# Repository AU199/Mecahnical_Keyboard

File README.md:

# Mecahnical Keyboard
I made this projects because I wanted to learn how software and hardware come together inside something as simple keyboard (Which I found wasn't simple at all). I wanted to also learn how to make a PCB and how to CAD with better practices. This is a Mechanical keyboard that utilizes both a main chip and a "slave" chip (a chip made to work as if it were just an i/o extender). This uses a diode-matrix for the sensing and uses the SDA and SCL channels on the "slave" chip to read and understand. 

BOM (Used an program for this to convert to a table in a .md file)
| Item                            | Description                                                 | Quantity | Total Price | shipping                                                                                                                                          | Link                                                                                                                                                                                                                                                                                                                                                                                                                                                                                                                                                                                                                                                                                                                                                                                                                                                                         | Running Total | Comments                                          |
| ------------------------------- | ----------------------------------------------------------- | -------- | ----------- | ------------------------------------------------------------------------------------------------------------------------------------------------- | ---------------------------------------------------------------------------------------------------------------------------------------------------------------------------------------------------------------------------------------------------------------------------------------------------------------------------------------------------------------------------------------------------------------------------------------------------------------------------------------------------------------------------------------------------------------------------------------------------------------------------------------------------------------------------------------------------------------------------------------------------------------------------------------------------------------------------------------------------------------------------- | ------------- | ------------------------------------------------- |
| Kailh Hotswap Switches (70 PCS) | Need for the mechanical Keyboard switches                   | 1        | $4.71       |                                                                                                                                                   | https://www.aliexpress.us/item/3256807290300019.html?spm=a2g0o.cart.0.0.655c38dakew0gR&mp=1&pdp_npi=5%40dis%21USD%21USD%2010.00%21USD%205.00%21%21USD%205.00%21%21%21%402103212b17669562373644915e8654%2112000040910888023%21ct%21US%216957464215%21%211%210&_gl=1*7n8lx*_gcl_aw*R0NMLjE3NjY5NTY1MjkuQ2owS0NRaUF4OFBLQmhEMUFSSXNBS3NtR2JmVFB0Uld6WHhSZGZYQmY2YmJCM0ppSWhiVndEci14TE1SelRfRDM4Y1R5UERmcTU4enRMc2FBaENJRUFMd193Y0I.*_gcl_dc*R0NMLjE3NjY5NTY1MjkuQ2owS0NRaUF4OFBLQmhEMUFSSXNBS3NtR2JmVFB0Uld6WHhSZGZYQmY2YmJCM0ppSWhiVndEci14TE1SelRfRDM4Y1R5UERmcTU4enRMc2FBaENJRUFMd193Y0I.*_gcl_au*MTg0MTgyOTEyNy4xNzY1OTI2NjE1*_ga*MTA1MDk4OTI5NS4xNzY2OTU0OTQ3*_ga_VED1YSGNC7*czE3NjY5NTQ5NDckbzEkZzEkdDE3NjY5NTY3ODgkajYwJGwwJGgw&gatewayAdapt=glo2usa                                                                                                                    | $4.71         |                                                   |
| 0.91 INCH OLED DISPLAY MODULE   | Display Module added for display functionallity             | 1        | $2.40       |                                                                                                                                                   | https://www.aliexpress.us/item/3256807115924372.html?spm=a2g0o.cart.0.0.200938daSMtqfN&mp=1&pdp_npi=6%40dis%21USD%21USD%204.81%21USD%202.36%21%21USD%202.08%21%21%21%402101d97817676331257023363ef25d%2112000040130675889%21ct%21US%216957464215%21%211%210%21&_gl=1*uoe70x*_gcl_aw*R0NMLjE3NjcwMjY4OTMuQ2owS0NRaUF4OFBLQmhEMUFSSXNBS3NtR2JmQUFHcUtNY3B5MU8xZEpYcC1KQmpCRi1yMkM3VEswRUFtMGNUUmZReU1lM1lSSjliV3RzY2FBakQ5RUFMd193Y0I.*_gcl_dc*R0NMLjE3NjcwMjY4OTMuQ2owS0NRaUF4OFBLQmhEMUFSSXNBS3NtR2JmQUFHcUtNY3B5MU8xZEpYcC1KQmpCRi1yMkM3VEswRUFtMGNUUmZReU1lM1lSSjliV3RzY2FBakQ5RUFMd193Y0I.*_gcl_au*MTg0MTgyOTEyNy4xNzY1OTI2NjE1*_ga*MTE3MjgzNDE0NC4xNzY3NTcxNTAx*_ga_VED1YSGNC7*czE3Njc2MzMxMTgkbzQkZzEkdDE3Njc2MzMxMjYkajUyJGwwJGgw&gatewayAdapt=glo2usa#nav-description                                                                                                 | $7.07         |                                                   |
| MCP23017-E/SO                   | I/O expander that I need in order to make the full keyboard | 1        | $4.99       |                                                                                                                                                   | https://www.aliexpress.us/item/3256810374801839.html?spm=a2g0o.productlist.main.2.77f5IXMhIXMhAF&algo_pvid=e8501886-1288-485f-a514-a1c879ddfb29&algo_exp_id=e8501886-1288-485f-a514-a1c879ddfb29-1&pdp_ext_f=%7B%22order%22%3A%22-1%22%2C%22eval%22%3A%221%22%2C%22fromPage%22%3A%22search%22%7D&pdp_npi=6%40dis%21USD%2113.11%210.99%21%21%2191.32%216.91%21%402101f11417669549847548423eec63%2112000052856422464%21sea%21US%210%21ABX%211%210%21n_tag%3A-29910%3Bd%3A1e4e634d%3Bm03_new_user%3A-29895%3BpisId%3A5000000187461913&curPageLogUid=8ompgAlH495t&utparam-url=scene%3Asearch%7Cquery_from%3A%7Cx_object_id%3A1005010561116591%7C_p_origin_prod%3A                                                                                                                                                                                                                | $12.06        |                                                   |
| XIAO-nRF52840                   | Main Chip of this keyboard                                  | 1        | $11.77      |                                                                                                                                                   | https://www.aliexpress.us/item/3256808117851584.html?spm=a2g0o.productlist.main.7.3ee7aNioaNioHj&algo_pvid=a97ae570-3fd6-4518-abb6-32d770b1e93e&algo_exp_id=a97ae570-3fd6-4518-abb6-32d770b1e93e-6&pdp_ext_f=%7B%22order%22%3A%22111%22%2C%22eval%22%3A%221%22%2C%22fromPage%22%3A%22search%22%7D&pdp_npi=6%40dis%21USD%2110.10%2110.10%21%21%2170.31%2170.31%21%402101df0e17669551094443275eda12%2112000044555521520%21sea%21US%210%21ABX%211%210%21n_tag%3A-29910%3Bd%3A1e4e634d%3Bm03_new_user%3A-29895&curPageLogUid=50eSLpqHWYKf&utparam-url=scene%3Asearch%7Cquery_from%3A%7Cx_object_id%3A1005008304166336%7C_p_origin_prod%3A                                                                                                                                                                                                                                        | $23.83        |                                                   |
| PCB & PCBA                      | The total price for both making the PCB and the PCBA        | 1        | $42.01      | $91.28 (FedEx Express (DDP), I can't do anything about the price, there is also a 10 dollar discount as such the grand total comes to be $123.85) | JLCPCB (CAN'T PROVIDE A LINK)                                                                                                                                                                                                                                                                                                                                                                                                                                                                                                                                                                                                                                                                                                                                                                                                                                                | $147.68       | includes Sales tax, shipping and customes duties  |
| Key Switch                      | Needed for typing                                           | 1        | $3.23       |                                                                                                                                                   | https://www.aliexpress.us/item/3256806499127042.html?spm=a2g0o.cart.0.0.119e38daoqse3D&mp=1&pdp_npi=5%40dis%21USD%21USD%2011.21%21USD%2011.21%21%21USD%2011.21%21%21%21%402101e80f17669585322435838ec12b%2112000038218653076%21ct%21US%216957464215%21%211%210&_gl=1*gffty9*_gcl_aw*R0NMLjE3NjY5NTgyNDguQ2owS0NRaUF4OFBLQmhEMUFSSXNBS3NtR2JmQUFHcUtNY3B5MU8xZEpYcC1KQmpCRi1yMkM3VEswRUFtMGNUUmZReU1lM1lSSjliV3RzY2FBakQ5RUFMd193Y0I.*_gcl_dc*R0NMLjE3NjY5NTgyNDguQ2owS0NRaUF4OFBLQmhEMUFSSXNBS3NtR2JmQUFHcUtNY3B5MU8xZEpYcC1KQmpCRi1yMkM3VEswRUFtMGNUUmZReU1lM1lSSjliV3RzY2FBakQ5RUFMd193Y0I.*_gcl_au*MTg0MTgyOTEyNy4xNzY1OTI2NjE1*_ga*MTA1MDk4OTI5NS4xNzY2OTU0OTQ3*_ga_VED1YSGNC7*czE3NjY5NTQ5NDckbzEkZzEkdDE3NjY5NTg1MzIkajUwJGwwJGgw&gatewayAdapt=glo2usa                                                                                                                 | $150.91       |                                                   |
| Key Caps                        | Needed to put on the swtiches                               | 1        | $8.77       |                                                                                                                                                   | https://www.aliexpress.us/item/3256804183268436.html?src=google&pdp_npi=4%40dis%21USD%2110.83%2110.83%21%21%21%21%21%40%2112000028934642287%21ppc%21%21%21&src=google&albch=shopping&acnt=179-224-6891&isdl=y&slnk=&plac=&mtctp=&albbt=Google_7_shopping&aff_platform=google&aff_short_key=_oFgTQeV&gclsrc=aw.ds&albagn=888888&ds_e_adid=&ds_e_matchtype=&ds_e_device=c&ds_e_network=x&ds_e_product_group_id=&ds_e_product_id=en3256804183268436&ds_e_product_merchant_id=563759696&ds_e_product_country=US&ds_e_product_language=en&ds_e_product_channel=online&ds_e_product_store_id=&ds_url_v=2&albcp=23114515373&albag=&isSmbAutoCall=false&needSmbHouyi=false&gad_source=1&gad_campaignid=23118775333&gbraid=0AAAABBR8xIeRvhWb_9Ku5wF_pep51_OBj&gclid=Cj0KCQiAx8PKBhD1ARIsAKsmGbfAAGqKMcpy1O1dJXp-JBjBF-r2C7TK0EAm0cTRfQyMe3YRJ9bWtscaAjD9EALw_wcB&gatewayAdapt=glo2usa | $159.68       |                                                   |
| Resistor Network (6PCS)         | Pull up Resistor chain                                      | 1        | $1.79       |                                                                                                                                                   | https://www.aliexpress.us/item/3256806684196291.html?spm=a2g0o.cart.0.0.655c38dakew0gR&mp=1&pdp_npi=5%40dis%21USD%21USD%202.70%21USD%201.78%21%21USD%201.78%21%21%21%402103212b17669562373644915e8654%2112000038573406947%21ct%21US%216957464215%21%211%210&_gl=1*1fbksrg*_gcl_aw*R0NMLjE3NjY5NTQ5NjAuQ2owS0NRaUF4OFBLQmhEMUFSSXNBS3NtR2JkbV9Wd1pDZUd1b0tJd0wyMzRhZ3BfWjdUb1V5MlZTeFBDbHkyYVUyby1vVXphWG84Uk1oc2FBdnY3RUFMd193Y0I.*_gcl_au*MTg0MTgyOTEyNy4xNzY1OTI2NjE1*_ga*MjI2OTg1MDkxLjE3NjY5NTU3NDY.*_ga_VED1YSGNC7*czE3NjY5NTU3NDUkbzEkZzEkdDE3NjY5NTY0NTUkajYwJGwwJGgw&gatewayAdapt=glo2usa                                                                                                                                                                                                                                                                            | $161.47       |                                                   |
| Soldering Wire (Lead Free)      | Needed For Soldering                                        | 1        | $3.65       |                                                                                                                                                   | https://www.aliexpress.us/item/3256810239367550.html?spm=a2g0o.productlist.main.3.6fae31a3JUGwVE&algo_pvid=2b9bc4d0-e253-4360-b2cb-9148e3e8c081&algo_exp_id=2b9bc4d0-e253-4360-b2cb-9148e3e8c081-2&pdp_ext_f=%7B%22order%22%3A%227%22%2C%22eval%22%3A%221%22%2C%22fromPage%22%3A%22search%22%7D&pdp_npi=6%40dis%21USD%217.54%210.99%21%21%2152.50%216.88%21%402101c44517669559046362254ed6dc%2112000052371160761%21sea%21US%216957464215%21ABX%211%210%21n_tag%3A-29910%3Bd%3A1e4e634d%3Bm03_new_user%3A-29895%3BpisId%3A5000000187461913&curPageLogUid=hSphYWSM5PaN&utparam-url=scene%3Asearch%7Cquery_from%3A%7Cx_object_id%3A1005010425682302%7C_p_origin_prod%3A                                                                                                                                                                                                         | $165.12       |                                                   |
| Stabalizers                     | Needed for the larger keys                                  | 1        | $6.77       | $16.50                                                                                                                                            | https://www.aliexpress.us/item/2251832533420646.html?spm=a2g0o.productlist.main.3.2c756ad92TU7VN&algo_pvid=b65fade0-7f1d-4251-948a-926cfa9af3fb&algo_exp_id=b65fade0-7f1d-4251-948a-926cfa9af3fb-2&pdp_ext_f=%7B%22order%22%3A%2217%22%2C%22eval%22%3A%221%22%2C%22fromPage%22%3A%22search%22%7D&pdp_npi=6%40dis%21USD%216.77%210.99%21%21%216.77%210.99%21%402101e2b617669566038303233e2e16%2165420166339%21sea%21US%216957464215%21ABX%211%210%21n_tag%3A-29910%3Bd%3A1e4e634d%3Bm03_new_user%3A-29895%3BpisId%3A5000000187461913&curPageLogUid=hNoizrgNcue8&utparam-url=scene%3Asearch%7Cquery_from%3A%7Cx_object_id%3A32719735398%7C_p_origin_prod%3A                                                                                                                                                                                                                    | $188.39       | includes Sales tax and shipping                   |
|                                 |
# SHIPPING PRICE PROOF (Price is a little different since I had to make a new order, but the delivery method is still the same)   

# PCB Image

#CAD Image

# 3D Render '0'

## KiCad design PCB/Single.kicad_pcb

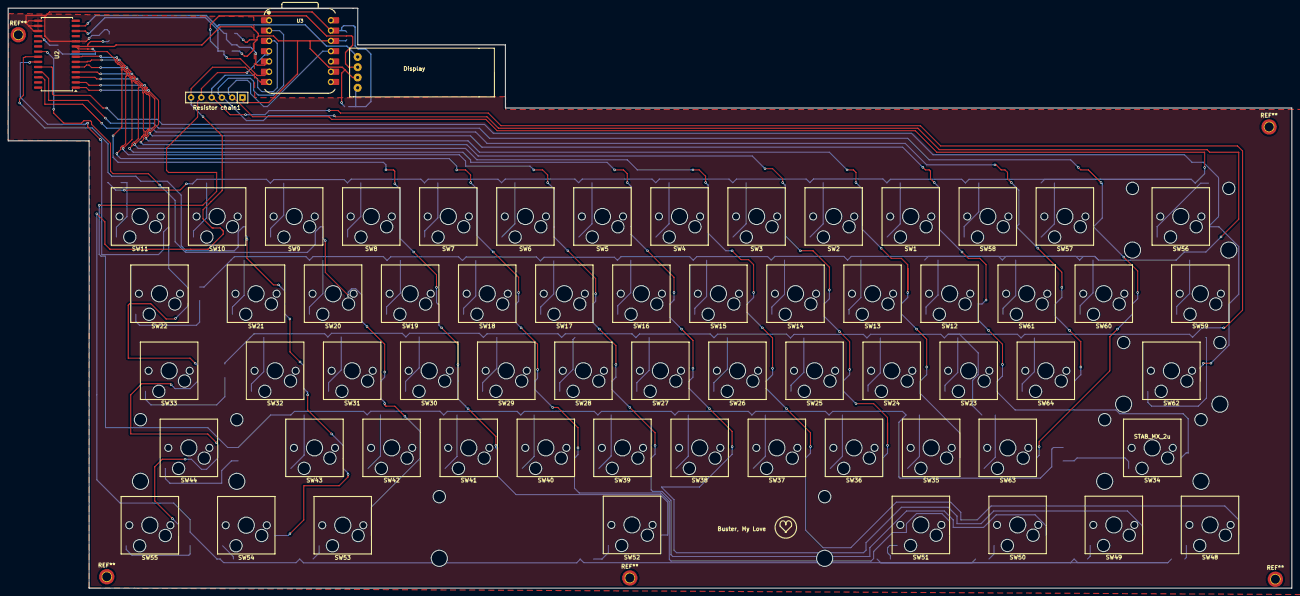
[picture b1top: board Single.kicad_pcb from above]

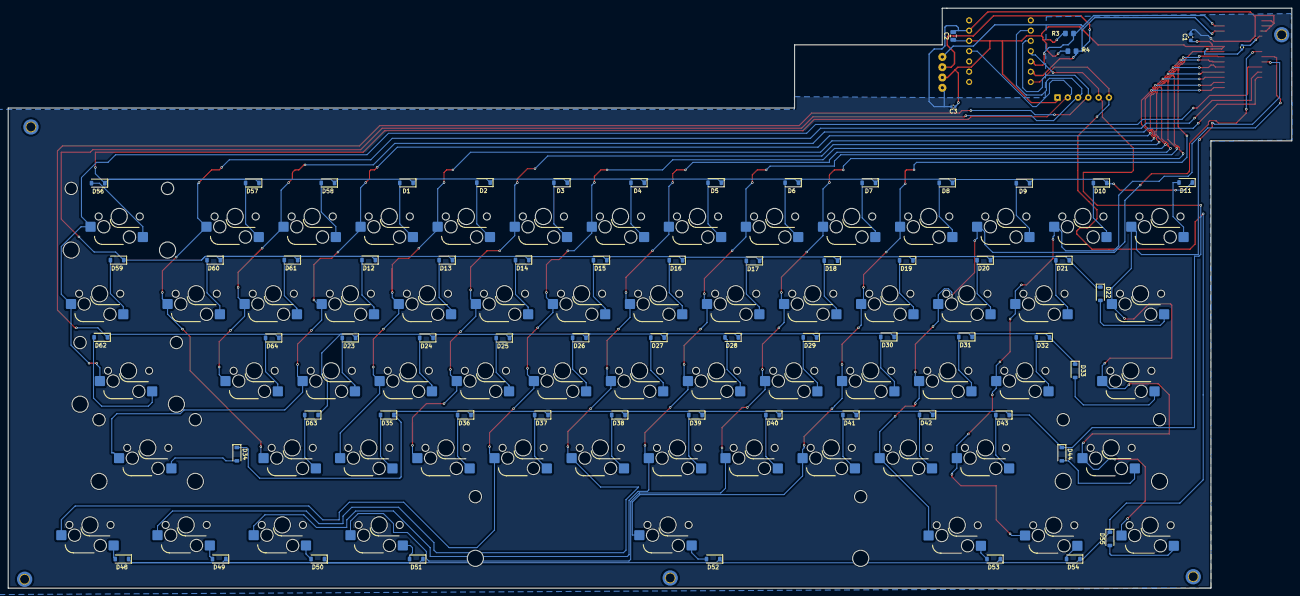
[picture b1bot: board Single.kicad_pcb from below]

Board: 2 copper layers, 317.3 x 143.3 mm, 132 parts (67 on the bottom side), 85 nets.

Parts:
C1: C1; C_0603_1608Metric
C2: C2; C_0805_2012Metric
C3: C_0402_1005Metric
D1, D2, D3, D4, D5, D6, D7, D8, D9, D10, D11, D12, D13, D14, D15, D16, D17, D18, D19, D20, D21, D22, D23, D24, D25, D26, D27, D28, D29, D30, D31, D32, D33, D34, D35, D36, D37, D38, D39, D40, D41, D42, D43, D44, D48, D49, D50, D51, D52, D53, D54, D55, D56, D57, D58, D59, D60, D61, D62, D63, D64: D; D_SOD-123
Display: MDOB128032GV-WI
R3, R4: R_45deg; R_0805_2012Metric_Pad1.20x1.40mm_HandSolder
R5: R_0402_1005Metric
Resistor chain1: R_Array_SIP6
SW1, SW2, SW3, SW4, SW5, SW6, SW7, SW8, SW9, SW10, SW11, SW12, SW13, SW14, SW15, SW16, SW17, SW18, SW19, SW20, SW21, SW23, SW24, SW25, SW26, SW27, SW28, SW29, SW30, SW31, SW32, SW35, SW36, SW37, SW38, SW39, SW40, SW41, SW42, SW43, SW57, SW58, SW60, SW61, SW63, SW64: SW_Push; SW_Hotswap_Kailh_MX_1.00u
SW22, SW59: SW_Push; SW_Hotswap_Kailh_MX_1.50u
SW33: SW_Push; SW_Hotswap_Kailh_MX_1.75u
SW34: SW_Push; SW_Hotswap_Kailh_MX_2.75u
SW44, SW62: SW_Push; SW_Hotswap_Kailh_MX_2.25u
SW48, SW49, SW50, SW51, SW53, SW54, SW55: SW_Push; SW_Hotswap_Kailh_MX_1.25u
SW52: SW_Push; SW_Hotswap_Kailh_MX_6.25u
SW56: SW_Push; SW_Hotswap_Kailh_MX_2.00u
U2: MCP23017_SO; SOIC-28W_7.5x17.9mm_P1.27mm
U3: XIAO-nRF52840-SMD; XIAO-nRF52840-DIP

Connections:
3V3: C1.1, C2.1, C3.1, Display.3, R3.1, R4.2, R5.1, Resistor chain1.1, U2.9 (VDD), U3.12 (3V3)
Col 1: SW56.1, SW59.1, SW62.1, U2.24 (GPA3)
Col 2: SW57.1, SW60.1, SW63.1, U2.25 (GPA4)
Col 3: SW58.1, SW61.1, SW64.1, U2.26 (GPA5)
Col 4: SW1.1, SW12.1, SW23.1, SW34.1, U2.1 (GPB0)
Col 5: SW2.1, SW13.1, SW24.1, SW35.1, U2.2 (GPB1)
Col 6: SW3.1, SW14.1, SW25.1, SW36.1, U2.3 (GPB2)
Col 7: SW4.1, SW15.1, SW26.1, SW37.1, SW48.1, U2.4 (GPB3)
Col 8: SW5.1, SW16.1, SW27.1, SW38.1, SW49.1, U2.5 (GPB4)
Col 9: SW6.1, SW17.1, SW28.1, SW39.1, SW50.1, U2.6 (GPB5)
Col 10: SW7.1, SW18.1, SW29.1, SW40.1, SW51.1, U2.7 (GPB6)
Col 11: SW8.1, SW19.1, SW30.1, SW41.1, SW52.1, U2.8 (GPB7)
Col 12: SW9.1, SW20.1, SW31.1, SW42.1, SW53.1, U2.21 (GPA0)
Col 13: SW10.1, SW21.1, SW32.1, SW43.1, SW54.1, U2.22 (GPA1)
Col 14: SW11.1, SW22.1, SW33.1, SW44.1, SW55.1, U2.23 (GPA2)
GND: C1.2, C2.2, C3.2, Display.4, U2.10 (VSS), U2.15 (A0), U2.16 (A1), U2.17 (A2), U3.13 (GND)
unnamed: D1.2 (A), SW1.2
unnamed: D2.2 (A), SW2.2
unnamed: D3.2 (A), SW3.2
unnamed: D4.2 (A), SW4.2
unnamed: D5.2 (A), SW5.2
unnamed: D6.2 (A), SW6.2
unnamed: D7.2 (A), SW7.2
unnamed: D8.2 (A), SW8.2
unnamed: D9.2 (A), SW9.2
unnamed: D10.2 (A), SW10.2
unnamed: D11.2 (A), SW11.2
unnamed: D12.2 (A), SW12.2
unnamed: D13.2 (A), SW13.2
unnamed: D14.2 (A), SW14.2
unnamed: D15.2 (A), SW15.2
unnamed: D16.2 (A), SW16.2
unnamed: D17.2 (A), SW17.2
unnamed: D18.2 (A), SW18.2
unnamed: D19.2 (A), SW19.2
unnamed: D20.2 (A), SW20.2
unnamed: D21.2 (A), SW21.2
unnamed: D22.2 (A), SW22.2
unnamed: D23.2 (A), SW23.2
unnamed: D24.2 (A), SW24.2
unnamed: D25.2 (A), SW25.2
unnamed: D26.2 (A), SW26.2
unnamed: D27.2 (A), SW27.2
unnamed: D28.2 (A), SW28.2
unnamed: D29.2 (A), SW29.2
unnamed: D30.2 (A), SW30.2
unnamed: D31.2 (A), SW31.2
unnamed: D32.2 (A), SW32.2
unnamed: D33.2 (A), SW33.2
unnamed: D34.2 (A), SW34.2
unnamed: D35.2 (A), SW35.2
unnamed: D36.2 (A), SW36.2
unnamed: D37.2 (A), SW37.2
unnamed: D38.2 (A), SW38.2
unnamed: D39.2 (A), SW39.2
unnamed: D40.2 (A), SW40.2
unnamed: D41.2 (A), SW41.2
unnamed: D42.2 (A), SW42.2
unnamed: D43.2 (A), SW43.2
unnamed: D44.2 (A), SW44.2
unnamed: D48.2 (A), SW48.2
unnamed: D49.2 (A), SW49.2
unnamed: D50.2 (A), SW50.2
unnamed: D51.2 (A), SW51.2
unnamed: D52.2 (A), SW52.2
unnamed: D53.2 (A), SW53.2
unnamed: D54.2 (A), SW54.2
unnamed: D55.2 (A), SW55.2
unnamed: D56.2 (A), SW56.2
unnamed: D57.2 (A), SW57.2
unnamed: D58.2 (A), SW58.2
unnamed: D59.2 (A), SW59.2
unnamed: D60.2 (A), SW60.2
unnamed: D61.2 (A), SW61.2
unnamed: D62.2 (A), SW62.2
unnamed: D63.2 (A), SW63.2
unnamed: D64.2 (A), SW64.2
Reset: R5.2, U2.18 (~RESET)
Row 1: D1.1 (K), D2.1 (K), D3.1 (K), D4.1 (K), D5.1 (K), D6.1 (K), D7.1 (K), D8.1 (K), D9.1 (K), D10.1 (K), D11.1 (K), D56.1 (K), D57.1 (K), D58.1 (K), Resistor chain1.2, U3.11 (P1.15_D10_MOSI)
Row 2: D12.1 (K), D13.1 (K), D14.1 (K), D15.1 (K), D16.1 (K), D17.1 (K), D18.1 (K), D19.1 (K), D20.1 (K), D21.1 (K), D22.1 (K), D59.1 (K), D60.1 (K), D61.1 (K), Resistor chain1.3, U3.2 (P0.03_A1_D1)
Row 3: D23.1 (K), D24.1 (K), D25.1 (K), D26.1 (K), D27.1 (K), D28.1 (K), D29.1 (K), D30.1 (K), D31.1 (K), D32.1 (K), D33.1 (K), D62.1 (K), D63.1 (K), D64.1 (K), Resistor chain1.4, U3.3 (P0.28_A2_D2)
Row 4: D34.1 (K), D35.1 (K), D36.1 (K), D37.1 (K), D38.1 (K), D39.1 (K), D40.1 (K), D41.1 (K), D42.1 (K), D43.1 (K), D44.1 (K), Resistor chain1.5, U3.4 (P0.29_A3_D3)
Row 5: D48.1 (K), D49.1 (K), D50.1 (K), D51.1 (K), D52.1 (K), D53.1 (K), D54.1 (K), D55.1 (K), Resistor chain1.6, U3.7 (P1.11_D6_TX)
SCL: Display.2, R4.1, U2.12 (SCK), U3.6 (P0.05_A5_D5_SCL)
SDA: Display.2, R3.2, U2.13 (SDA), U3.5 (P0.04_A4_D4_SDA)

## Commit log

2025-12-26 Added all PCB files
2025-12-26 Moved everything into the PCB folder
2025-12-26 Fix typo in project title
2025-12-28 Added the images and stl file
2025-12-28 fixed essentially everything
2025-12-28 added the new keyboard Assembly
2025-12-28 Updated the README
2025-12-28 fixed the table formating
2025-12-28 Added a few items and the library that was used
2025-12-28 Add CAD file link to CADFileLink.txt
2025-12-28 Added firmware
2025-12-28 Add note regarding STL file size and link
    Added a note about the STL file size and provided a link.
2025-12-28 Create references.txt for project guidance
    Added references to AI guidance and learning resources.
2025-12-28 Add references document detailing AI usage and learning resources
2025-12-28 Add PCB, CAD, and 3D render images to README
    Added images of PCB, CAD, and a 3D render to the README.
2025-12-28 fixed README
2025-12-28 Updated both README and BOM
2025-12-28 ALI EXPRESS
2025-12-29 Add CAD file link, update README with improved BOM formatting, and correct references
2025-12-29 Revise PCB and PCBA cost information
    Updated the PCB and PCBA cost details in the README.
2025-12-29 Fix formatting and update PCB cost details in README
2025-12-31 Clarify BOM details and pricing notes in README
    Updated the README to clarify the BOM and added notes about pricing.
2026-01-02 Fix formatting and descriptions in README.md
    Updated the README to correct formatting and clarify item descriptions in the BOM.
2026-01-03 Add shipping price proof and images section
    Added shipping price proof section and PCB/CAD images.
2026-01-03 Add shipping price proof images
    Added shipping price proof images to the README.
2026-01-03 Rename Screenshot 2026-01-01 214915.png to Screenshot_2026-01-01_214915.png
2026-01-03 Rename Screenshot 2026-01-01 214928.png to Screenshot_2026-01-01_214928.png
2026-01-03 Revise shipping price proof and add images
    Updated shipping price proof section with new images and clarified the note about price differences.
2026-01-03 Rename invoice.png to Invoice.png
2026-01-06 added the display code, will be adding more functionallity, but basic code in
2026-01-06 Added all files required for the display based keyboard
2026-01-06 update Invoice
2026-01-06 Rename Invoice.png to NewInvoice.png
2026-01-06 Replace old invoice image with new invoice
    Updated the shipping price proof image in README.
2026-01-08 Refactor code structure for improved readability and maintainability
2026-01-08 updated BOM
2026-01-08 updated gerber
